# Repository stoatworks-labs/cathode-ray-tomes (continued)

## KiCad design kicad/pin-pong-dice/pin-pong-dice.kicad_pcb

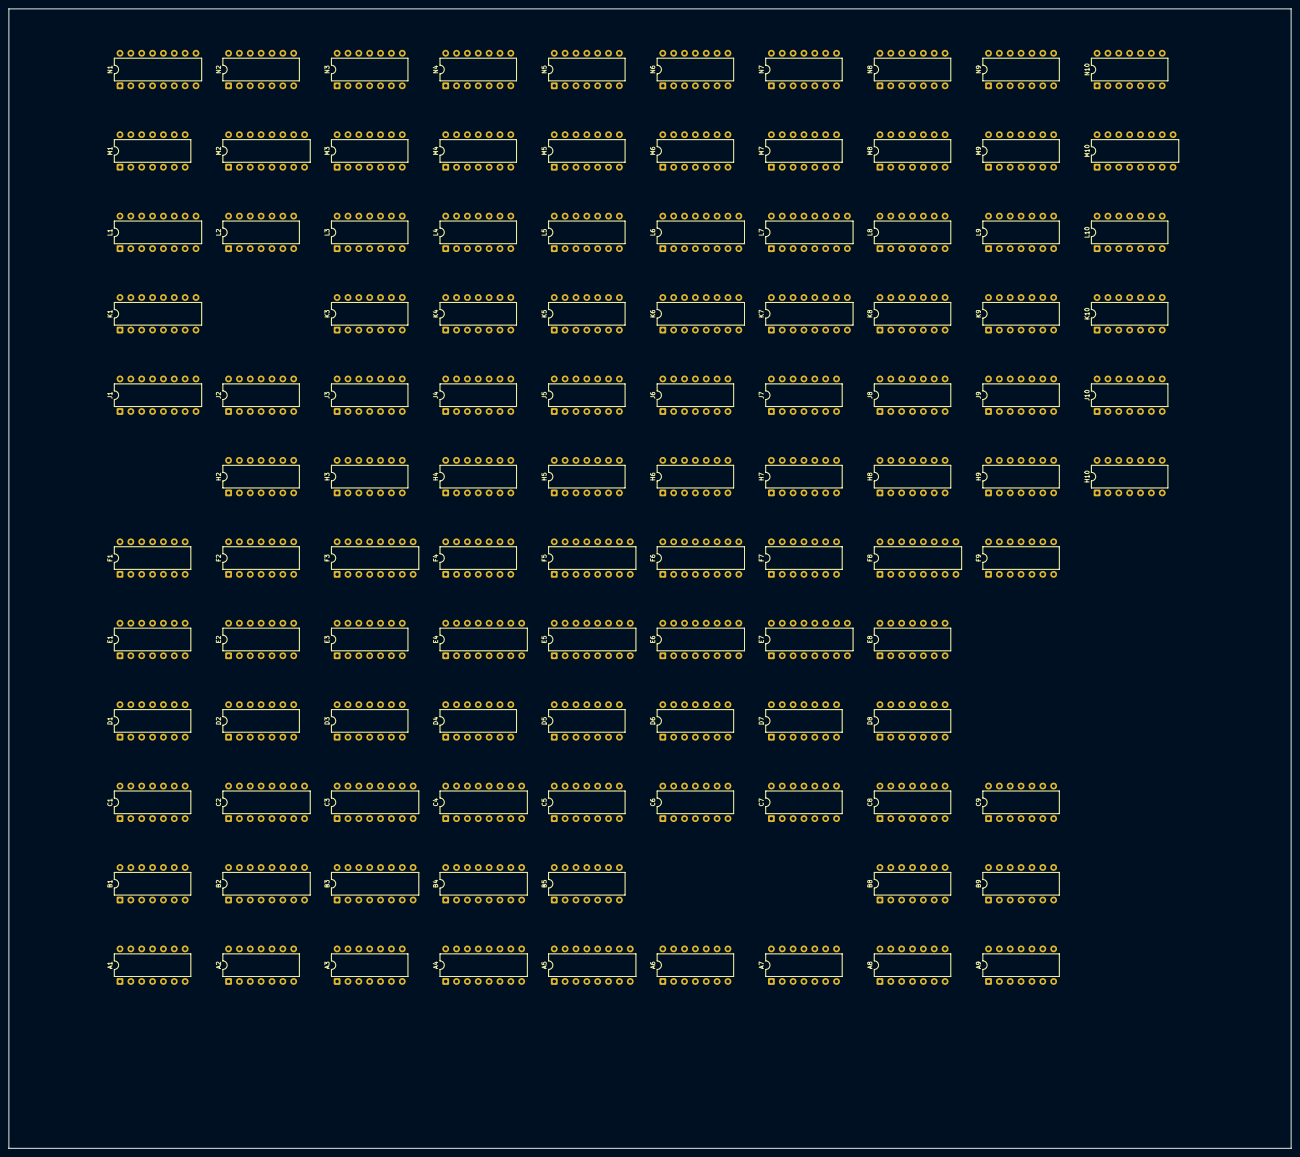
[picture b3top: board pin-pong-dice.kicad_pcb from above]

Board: 2 copper layers, 300.0 x 266.6 mm, 108 parts (0 on the bottom side), 357 nets, no tracks yet.

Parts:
A1, A2: 7474; DIP-14_W7.62mm
A3: 7486; DIP-14_W7.62mm
A4: 9314; DIP-16_W7.62mm
A5: 9602; DIP-16_W7.62mm
A6: 7400; DIP-14_W7.62mm
A7: 7410; DIP-14_W7.62mm
A8: 7402; DIP-14_W7.62mm
A9: 7408; DIP-14_W7.62mm
B1: 7420; DIP-14_W7.62mm
B2, B3: 74193; DIP-16_W7.62mm
B4: 9322; DIP-16_W7.62mm
B5: 7474; DIP-14_W7.62mm
B8: 7410; DIP-14_W7.62mm
B9: 7402; DIP-14_W7.62mm
C1: 7474; DIP-14_W7.62mm
C2, C3: 74193; DIP-16_W7.62mm
C4: 9322; DIP-16_W7.62mm
C5, C8: 7400; DIP-14_W7.62mm
C6, C7: 7490; DIP-14_W7.62mm
C9: 7432; DIP-14_W7.62mm
D1, D3: 7408; DIP-14_W7.62mm
D2: 7474; DIP-14_W7.62mm
D4: 7493; DIP-14_W7.62mm
D5: 7486; DIP-14_W7.62mm
D6, D7: 7490; DIP-14_W7.62mm
D8: 7420; DIP-14_W7.62mm
E1: 7474; DIP-14_W7.62mm
E2: 7402; DIP-14_W7.62mm
E3: 7486; DIP-14_W7.62mm
E4: 74193; DIP-16_W7.62mm
E5: 9312; DIP-16_W7.62mm
E6, E7: 74153; DIP-16_W7.62mm
E8: 74107; DIP-14_W7.62mm
F1, F9: 7474; DIP-14_W7.62mm
F2, F4: 7400; DIP-14_W7.62mm
F3: 9316; DIP-16_W7.62mm
F5: 9312; DIP-16_W7.62mm
F6: 7448; DIP-16_W7.62mm
F7: 7402; DIP-14_W7.62mm
F8: 9322; DIP-16_W7.62mm
H2: 7404; DIP-14_W7.62mm
H3: 7410; DIP-14_W7.62mm
H4: 7402; DIP-14_W7.62mm
H5, H7: 7474; DIP-14_W7.62mm
H6: 7486; DIP-14_W7.62mm
H8: 74107; DIP-14_W7.62mm
H9: 7408; DIP-14_W7.62mm
H10: 7400; DIP-14_W7.62mm
J1: 9321; DIP-16_W7.62mm
J2: 7420; DIP-14_W7.62mm
J3: 7430; DIP-14_W7.62mm
J4: 7404; DIP-14_W7.62mm
J5: 7408; DIP-14_W7.62mm
J6, J10: 7410; DIP-14_W7.62mm
J7, J9: 7474; DIP-14_W7.62mm
J8: 7427; DIP-14_W7.62mm
K1: 9314; DIP-16_W7.62mm
K3: 7486; DIP-14_W7.62mm
K4, K8: 7404; DIP-14_W7.62mm
K5: 7420; DIP-14_W7.62mm
K6: 9316; DIP-16_W7.62mm
K7: 7485; DIP-16_W7.62mm
K9, K10: 7474; DIP-14_W7.62mm
L1: 9314; DIP-16_W7.62mm
L2, L4: 7400; DIP-14_W7.62mm
L3, L10: 7402; DIP-14_W7.62mm
L5: 7427; DIP-14_W7.62mm
L6: 9316; DIP-16_W7.62mm
L7: 7485; DIP-16_W7.62mm
L8: 74107; DIP-14_W7.62mm
L9: 7410; DIP-14_W7.62mm
M1: 7430; DIP-14_W7.62mm
M2: 74157; DIP-16_W7.62mm
M3, M5, M6: 7474; DIP-14_W7.62mm
M4, M9: 7408; DIP-14_W7.62mm
M7: 7486; DIP-14_W7.62mm
M8: 7493; DIP-14_W7.62mm
M10: 9312; DIP-16_W7.62mm
N1: 9312; DIP-16_W7.62mm
N2: 7400; DIP-14_W7.62mm
N3: 7408; DIP-14_W7.62mm
N4: 7474; DIP-14_W7.62mm
N5: 7410; DIP-14_W7.62mm
N6, N7: 7486; DIP-14_W7.62mm
N8: 7493; DIP-14_W7.62mm
N9: 7420; DIP-14_W7.62mm
N10: 74164; DIP-14_W7.62mm

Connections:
+5V: A1.14, A2.14, A3.14, A6.14, A7.14, A8.14, A9.14, B1.14, B2.16, B3.16, B4.16, B5.14, B8.14, B9.14, C1.14, C2.16, C3.16, C4.16, C5.14, C6.5, C7.5, C8.14, C9.14, D1.14, D2.14, D3.14, D4.5, D5.14, D6.5, D7.5, D8.14, E1.14, E2.14, E3.14, E4.16, E5.16, E6.16, E7.16, E8.14, F1.14, F2.14, F3.16, F4.14, F5.16, F6.16, F7.14, F8.16, F9.14, H2.14, H3.14, H4.14, H5.14, H6.14, H7.14, H8.14, H9.14, H10.14, J1.16, J2.14, J3.14, J4.14, J5.14, J6.14, J7.14, J8.14, J9.14, J10.14, K3.14, K4.14, K5.14, K6.16, K7.16, K8.14, K9.14, K10.14, L2.14, L3.14, L4.14, L5.14, L6.16, L7.16, L8.14, L9.14, L10.14, M1.14, M2.16, M3.14, M4.14, M5.14, M6.14, M7.14, M8.5, M9.14, M10.16, N1.16, N2.14, N3.14, N4.14, N5.14, N6.14, N7.14, N8.5, N9.14, N10.14
A1-1: A1.1, A1.9
A1-2: A1.2, B1.8
A1-3: A1.3, B3.5, D1.11
A1-5: A1.5, A2.1, A2.13, B2.11, B3.11
A2-2: A2.2, A2.6, A2.11
A2-3: A2.3, B2.12
A2-8: A2.8, A2.12
A2-9: A2.9, B1.9, E1.3
A3-1: A3.1, A4.13
A3-3: A3.3, B3.1
A3-4: A3.4, A4.12
A3-6: A3.6, B3.10
A3-8: A3.8, B3.9
A3-10: A3.10, A4.10
A3-11: A3.11, B3.15
A3-13: A3.13, A4.15
A4-1: A4.1, N2.8, N3.12
A4-4: A4.4, C4.9
A4-6: A4.6, C4.12
A5-4: A5.4, A8.1
A5-10: A5.10, F1.11, L4.2
A5-12: A5.12, D8.8
A5-13: A5.13, L4.3
A6-11: A6.11, F7.11
A7-1: A7.1, F8.9
A7-2: A7.2, F8.7
A7-10: A7.10, A8.13
A7-11: A7.11, A8.10
A8-3: A8.3, A8.4
A8-5: A8.5, K7.7
A8-6: A8.6, F8.12
A8-9: A8.9, F4.6, L10.3, M4.1
A8-12: A8.12, M9.6
A9-1: A9.1, A9.4, A9.10, F1.9
A9-3: A9.3, C7.14
A9-8: A9.8, D5.12
A9-11: A9.11, L4.1
ATTRACT: B9.9, F8.15, H9.4, J9.5
ATTRACT_n: J8.1, J9.6, J10.1, J10.11, N3.4
B1-1: B1.1, C2.7
B1-2: B1.2, D1.8
B1-4: B1.4, C1.5, E1.11
B1-5: B1.5, C1.9
B1-6: B1.6, D2.12
B1-10: B1.10, B2.3
B1-12: B1.12, B3.7, E2.5
B1-13: B1.13, B3.6
B2-5: B2.5, B3.12
B4-4: B4.4, C4.2
B4-7: B4.7, C4.5
B4-9: B4.9, C4.11
B4-12: B4.12, C4.14
B5-5: B5.5, J8.2
B5-6: B5.6, H4.12
B5-13: B5.13, C5.11
B8-6: B8.6, B8.10, D8.10
B8-8: B8.8, E2.11
B8-9: B8.9, C8.8, D8.9
B8-11: B8.11, C8.3, D8.12
B9-1: B9.1, C9.1
B9-2: B9.2, C5.3, D5.2
B9-4: B9.4, C9.4
B9-8: B9.8, F9.8, L10.9
B9-10: B9.10, K10.13
B9-11: B9.11, B9.12, H9.5
B9-13: B9.13, L10.12
BALL: A9.12, B8.5, C8.2, C8.4, C8.10, E1.9, F4.1, H9.13, J10.5, L4.4
BALLS_REMAINING_n: L9.12, N2.1
BALL_BLANKING: H10.2, J10.12
BALL_BLANKING_n: F2.10, H10.3, J10.13, L10.11
BALL_n: E1.8, J1.15
C1-1: C1.1, C1.13, C2.11, C3.11, D2.9
C1-2: C1.2, C1.6
C1-3: C1.3, C1.8, C1.12
C1-4: C1.4, C1.10, D2.5, D2.13
C1-11: C1.11, C2.12
C2-3: C2.3, D1.9
C2-5: C2.5, C3.12
C2-14: C2.14, C3.14, D2.6
C2-15: C2.15, F2.11
C3-1: C3.1, D3.3
C3-2: C3.2, D1.10
C3-7: C3.7, E2.9
C3-9: C3.9, D3.8
C3-10: C3.10, D3.6
C3-15: C3.15, D3.11
C4-1: C4.1, D1.3
C4-4: C4.4, E4.9
C4-7: C4.7, E4.10
C5-2: C5.2, C5.6
C5-4: C5.4, E5.14
C5-5: C5.5, F5.14
C6-1: C6.1, C6.12, E7.5
C6-8: C6.8, E6.5
C6-9: C6.9, E7.11
C6-11: C6.11, E6.11
C6-14: C6.14, D6.11, E6.10
C7-1: C7.1, C7.12, E7.4
C7-8: C7.8, E6.4
C7-9: C7.9, E7.12
C7-11: C7.11, D5.13, E6.12
C8-1: C8.1, C9.6
C8-5: C8.5, C9.3
C8-6: C8.6, D8.13
C9-10: C9.10, D5.6
CLK: H7.5, K6.2, L6.2, M5.11, N4.3
CLK_n: H7.2, H7.6, J1.14, J7.3, L7.3
CROSS: K4.5, L4.8
CROSS_CENTER_FLASHING: A9.13, C9.2, J5.8
CROSS_ZONE: D8.2, K4.2, L4.5, L4.13
CROSS_ZONE_n: J2.4, K4.1, K5.6, L3.2, L3.8
CROSS_n: H3.5, K4.6
D3-2: D3.2, E3.11
D3-5: D3.5, E3.8
D3-9: D3.9, E3.6
D3-12: D3.12, E3.3
D4-14: D4.14, L2.11
D5-3: D5.3, D5.4
D5-5: D5.5, H4.13
D5-8: D5.8, D6.14
D5-10: D5.10, D7.11, E6.13
D5-11: D5.11, D7.14
D6-1: D6.1, D6.12, E7.6
D6-8: D6.8, E6.6
D6-9: D6.9, E7.10
D7-1: D7.1, D7.12, E7.3
D7-8: D7.8, E6.3
D7-9: D7.9, E7.13
D8-4: D8.4, L5.8
D8-6: D8.6, L3.11, L4.9
E1-4: E1.4, E2.4
E1-5: E1.5, E2.8
E1-13: E1.13, E2.10
E2-6: E2.6, F2.8
E2-12: E2.12, H9.11
E2-13: E2.13, H2.9
E3-1: E3.1, E4.3
E3-4: E3.4, E4.7, H2.11
E3-10: E3.10, E4.6
E3-13: E3.13, E4.2
E4-4: E4.4, F2.3
E4-5: E4.5, H3.8
E4-11: E4.11, N3.11
E4-13: E4.13, M3.4, N4.10
E4-14: E4.14, N4.9
E5-1: E5.1, F6.13
E5-4: E5.4, F6.14
E5-9: E5.9, F6.10
E6-1: E6.1, E6.15, E7.1, E7.15, F7.13, J4.11
E6-7: E6.7, F6.2
E6-9: E6.9, F6.6
E7-7: E7.7, F6.7
E7-9: E7.9, F6.1
E8-1: E8.1, E8.6, E8.11
E8-2: E8.2, F8.10
E8-3: E8.3, E8.8, F8.3
E8-4: E8.4, E8.5, F8.6
E8-10: E8.10, E8.13, F8.13
F1-2: F1.2, N1.14
F1-5: F1.5, F2.5
F2-4: F2.4, H2.4
F4-2: F4.2, H4.1
F4-8: F4.8, H4.9
F4-10: F4.10, F4.11
F4-12: F4.12, J4.10
F5-1: F5.1, F6.12
F5-3: F5.3, F6.11
F5-6: F5.6, F6.15
F5-9: F5.9, F6.9
F8-2: F8.2, H8.3, H8.8
F8-5: F8.5, H8.4, H8.5
F8-11: F8.11, H8.2
F8-14: F8.14, H8.10, H8.13
F9-2: F9.2, H9.1, K8.9
F9-4: F9.4, F9.10, H9.8
F9-5: F9.5, F9.12
FLIPPER: A5.6, C9.5, H4.5
FLIPPER_HIT_WINDOW: A5.3, B5.9
FLIPPER_HIT_WINDOW_n: B5.8, B9.6
FLIPPER_MOTION: B4.3, B4.10, F8.4, H10.12, H10.13
FLIPPER_MOTION_CLOCK: E8.9, E8.12, F3.13, H8.9, H8.12
FLIPPER_MOTION_n: B9.5, H10.11
FLIPPER_WINDOW: A7.13, B5.11, H2.2
FLIPPER_WINDOW_n: A7.8, A8.2, C5.12, D1.2, H2.1
FLIP_UP_n: A7.12, J2.13
FREE_BALL_INDICATOR: D5.1, K10.6, L10.6
FREE_BALL_SWITCHED_n: B9.3, K10.1
GND: A1.7, A2.7, A3.7, A4.2, A4.5, A4.7, A4.11, A4.14, A6.7, A7.7, A8.7, A9.7, B1.7, B2.1, B2.8, B2.9, B2.10, B2.14, B3.8, B3.14, B4.8, B4.13, B4.15, B5.2, B5.7, B8.7, B9.7, C1.7, C2.1, C2.8, C2.9, C2.10, C3.8, C4.3, C4.8, C4.15, C5.7, C6.6, C6.7, C6.10, C7.6, C7.7, C7.10, C8.7, C9.7, D1.7, D2.7, D3.7, D4.2, D4.3, D4.10, D5.7, D6.6, D6.7, D6.10, D7.6, D7.7, D7.10, D8.7, E1.2, E1.7, E2.7, E3.7, E4.8, E5.2, E5.3, E5.5, E5.6, E5.7, E5.8, E6.8, E7.8, E8.7, F1.7, F2.7, F3.4, F3.5, F3.8, F4.7, F5.2, F5.4, F5.5, F5.7, F5.8, F6.8, F7.7, F8.8, F9.7, H2.7, H3.7, H4.7, H5.7, H6.7, H7.7, H8.7, H9.7, H10.7, J1.8, J2.7, J3.7, J4.7, J5.7, J6.7, J7.7, J8.7, J9.7, J10.7, K3.7, K4.7, K5.7, K6.8, K7.1, K7.3, K7.8, K7.13, K7.14, K7.15, K8.7, K9.7, K10.7, L2.7, L3.7, L4.7, L5.7, L6.8, L7.2, L7.4, L7.8, L8.7, L9.7, L10.7, L10.8, M1.7, M2.8, M3.7, M4.7, M5.7, M6.7, M7.7, M8.10, M9.7, M10.8, M10.10, N1.8, N1.10, N2.7, N3.7, N4.7, N4.12, N5.7, N6.7, N7.7, N8.10, N9.7, N10.7
GRAVITY: F3.9, H2.12, H3.10, H4.11, N4.11
GRAVITY_n: F2.2, F3.15, H2.13, J5.10
H1: K5.10, L6.14, L7.9
H2: E5.11, J5.13, K8.3, L6.13, L7.11
H2-3: H2.3, J3.8
H2-5: H2.5, J2.8
H2-6: H2.6, M2.11
H2-10: H2.10, H3.9
H2_n: D8.1, K8.4
H4: E5.12, J8.5, L5.10, L6.12, L7.14
H4-2: H4.2, H5.1, J6.6
H5-3: H5.3, J5.11
H5-11: H5.11, J5.6
H5-13: H5.13, J6.12
H6-3: H6.3, J6.11
H6-8: H6.8, J4.3
H6-11: H6.11, L5.1
H6-12: H6.12, K7.2, L7.7
H8: E5.13, F1.3, F5.12, L5.11, L6.11, L7.1, M10.11
H8-1: H8.1, H8.6, H8.11
H9-2: H9.2, J9.13, K8.10, K9.10
H9-3: H9.3, J9.4
H9-6: H9.6, J9.12
H9-9: H9.9, K8.8
H16: C5.1, C5.13, H6.1, H6.13, H7.11, J3.2, J5.5, J6.1, K6.14, K7.9, L5.9, M10.12, N6.2
H32: D8.5, H6.2, H6.9, H7.12, J1.2, J5.1, J6.2, J6.3, K6.13, K8.5, N1.11
H32H64: H3.2, J2.1, J5.3, J5.12
H32_n: K7.11, K8.6, M10.13
H32_xor_H64_n: F4.4, J4.4, N2.12
H64: A7.9, F7.2, H6.10, J1.3, J5.2, K5.1, K5.12, K6.12, L5.13, N1.12
H128: A8.8, D1.12, J3.1, J5.4, J6.4, K5.2, K5.13, K6.11
H256: D2.3, F4.5, J6.5, J6.13, J9.11, K5.9, L8.5, N5.1
H256_n: H3.13, H5.12, J2.2, J10.3, K3.2, L8.6, M2.3, N7.9
HBLANK: F7.1, F7.5, H7.10
HBLANK_n: F7.3, F7.4
HFIELD: H5.5, N3.1, N5.5
HIT: H2.8, J2.10, M2.10, M4.9, N2.10
HRESET: F7.6, J7.6, M9.10
HRESET_n: J7.5, K6.1, L6.1, L8.10
HSCORE_WINDOW: H3.12, H4.8, N3.2
H_UP: E3.2, E3.5, E3.9, E3.12, F2.12, F3.3, H3.11, M3.5
H_UP_n: F2.1, M3.6
INCREMENT_1000: A9.6, D5.9, M5.3
J1-4: J1.4, K1.2, L1.2
J1-5: J1.5, K1.14, L1.14
J1-6: J1.6, K1.5, L1.5
J1-7: J1.7, K1.11, L1.11
J1-9: J1.9, L1.1
J1-11: J1.11, K1.1
J2-6: J2.6, J2.9
J4-5: J4.5, L3.10
J4-6: J4.6, N3.10
J5-9: J5.9, L3.13
J6-8: J6.8, L5.2
J7-2: J7.2, K5.8
J7-11: J7.11, M8.14, M9.8
J7-12: J7.12, L9.6
J8-3: J8.3, L9.8
J8-6: J8.6, L9.2
J8-12: J8.12, K9.3, K9.11
J9-3: J9.3, M9.11
J10-6: J10.6, J10.10
K1-10: K1.10, M1.11, N1.9
K1-12: K1.12, M1.12, N1.7
K1-13: K1.13, M1.6, N1.6
K1-15: K1.15, M1.5, N1.5
K3-1: K3.1, K7.5
K3-3: K3.3, M4.2
K4-4: K4.4, K5.5
K6-7: K6.7, L6.15
K6-15: K6.15, L8.9
K7-4: K7.4, L7.5
K9-1: K9.1, K9.13, L10.10
K9-5: K9.5, K9.12
K10-5: K10.5, M9.1
K10-12: K10.12, L10.13
KNOCKDOWNS_n: F2.6, H3.3, J1.1
L1-10: L1.10, M1.4, N1.4
L1-12: L1.12, M1.3, N1.3
L1-13: L1.13, M1.2, N1.2
L1-15: L1.15, M1.1, N1.1
L2-3: L2.3, L2.4
L2-5: L2.5, L2.8
L2-6: L2.6, M2.14
L3-1: L3.1, L5.4
L3-4: L3.4, L5.3, M2.15
L3-5: L3.5, L4.6
L5-5: L5.5, M4.11
L5-6: L5.6, M4.10
L5-12: L5.12, M5.12
L7-10: L7.10, M7.8
L7-12: L7.12, M7.6
L7-13: L7.13, M7.11
L7-15: L7.15, M7.3
L9-1: L9.1, M10.14
L9-13: L9.13, L10.1
L10-4: L10.4, M9.12
M2-2: M2.2, N2.11
M2-4: M2.4, M3.2
M2-5: M2.5, N3.8
M2-6: M2.6, N2.6
M2-7: M2.7, N2.9
M2-9: M2.9, M3.11
M2-12: M2.12, M3.12
M3-3: M3.3, M4.8
M4-3: M4.3, N4.2
M5-2: M5.2, M5.6, N5.2
M5-9: M5.9, N5.10
M6-5: M6.5, N6.12
M7-2: M7.2, M7.5, M7.9, M7.12, N6.3
M9-3: M9.3, N10.8
M10-1: M10.1, N10.3
M10-2: M10.2, N10.4
M10-3: M10.3, N10.5
MISS_n: F4.3, J10.2, L10.5, N3.5
MISS_nor_ATTRACT: K1.9, L1.9, M5.1, N3.6
N2-13: N2.13, N3.3, N3.9
N4-5: N4.5, N5.4
N5-11: N5.11, N5.12
N6-1: N6.1, N7.3
N7-5: N7.5, N7.8, N7.12
PLAYFIELD_n: B8.3, H9.12, N2.2, N5.6
R0: C4.13, D4.1, D4.12, E4.15
R1: A4.3, D4.9
R2: C4.10, D4.8
R3: C4.6, D4.11, E4.1, L3.6
SCORE_WINDOW: F6.4, H4.10, J4.9
SCORE_WINDOW_n: C9.9, J4.8
SERVE: H4.3, H10.6, J4.1, J10.9
SERVE_BUFF_n: F3.10, J4.2
SERVE_RESET: K10.9, M9.2
SERVE_RESET_n: A1.13, D2.1, H10.1, H10.4, K10.8
SERVE_n: A4.9, B4.1, D1.1, F1.12, H10.5, J10.8, K10.3, M3.1, M3.13, N2.5, N3.13
SLINGSHOTS: B8.4, M4.6, N4.4
START: C6.2, C6.3, C7.2, C7.3, D6.2, D6.3, D7.2, D7.3, J8.13, J9.9
START_n: B5.3, J9.1, J9.8, K10.4, N10.9
THUMPER_BUMPERS_n: H3.4, N5.8
V1: L2.12, M7.10, M8.1, M8.12
V2: F5.11, L2.13, L9.4, M6.3, M7.4, M8.9
V4: F5.13, J3.6, L9.3, L9.10, M7.13, M8.8
V8: J3.5, K8.1, M7.1, M8.11, N8.14
V8_n: E5.10, F5.10, F7.9, J8.4, K8.2
V16: A6.12, E6.14, E7.14, J3.4, M6.11, N6.10, N7.1, N7.4, N8.1, N8.12, N9.9
V16_xor_V32: J3.3, J6.10, N6.8
V16_xor_V128: K7.10, M9.4, N7.6
V32: E6.2, E7.2, F7.12, L2.9, N6.9, N7.13, N8.9, N9.12
V32_xor_V128: B4.6, F4.13, K4.3, K7.12, M9.5, N5.13, N7.11
V64: A6.13, N6.5, N8.8, N9.13
V128: F9.3, F9.11, J8.9, J8.10, J8.11, L8.12, M6.2, N1.13, N6.4, N6.13, N7.10, N8.11, N9.10
V128_n: F8.1, J1.13, J8.8, L2.2, L9.9, M2.13
V240: F7.8, M6.13, N9.8
V256: K10.11, L8.3, L9.5
VCC: A1.4, A1.10, A1.12, A2.4, A2.10, A5.5, A5.11, B2.4, B3.4, B4.2, B4.5, B4.11, B4.14, B5.1, B5.4, B5.10, B5.12, C2.4, C3.4, D1.13, D2.2, D2.4, D2.10, E1.1, E1.10, E1.12, F1.1, F1.4, F1.10, F2.9, F3.1, F3.6, F3.7, F6.3, F6.5, F9.1, F9.13, H5.2, H5.4, H5.10, H7.1, H7.4, H7.13, H9.10, J2.5, J7.1, J7.4, J7.10, J7.13, J9.2, J9.10, K1.3, K1.4, K1.6, K1.7, K6.9, K6.10, K9.2, K10.2, K10.10, L1.3, L1.4, L1.6, L1.7, L6.7, L6.9, L6.10, L8.1, L8.4, L8.8, L8.11, M3.10, M5.4, M5.10, M5.13, M6.1, M6.4, M6.10, M6.12, M9.9, M10.6, M10.7, M10.9, N4.1, N4.13, N10.1, N10.2
VCROSS: L3.3, L3.9, L4.12, N6.11
VCROSS_n: J2.12, L3.12, L4.10, L4.11
VFIELD: A1.11, M6.9, N5.3
VFIELD_n: L9.11, M6.8
VRESET: D3.1, D3.4, D3.10, D3.13, F2.13, J7.8, M8.2, M8.3, N8.2, N8.3
VRESET_n: F1.13, J7.9, L8.13
VSYNC: F3.2, F7.10
V_UP: A3.2, A3.5, A3.9, A3.12, M3.9
V_UP_n: B2.15, M3.8
ZONEH: H5.9, J3.11, J10.4, L2.10, L10.2, M4.12, N2.4, N5.9, N7.2
ZONEH_n: H3.1, H5.8, L2.1, M4.5
ZONEV: F4.9, J6.9, K4.9, K5.4, N6.6
ZONEV_n: A8.11, J3.12, K4.8, M2.1, M4.4, M4.13
_2CLOCK: C3.5, D2.11, H7.3
_100_POINT_OBJECTS: C8.9, H3.6, H4.6
